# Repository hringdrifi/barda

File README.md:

# Blað

Blað is a compact wireless keyboard design project by [hringdrifi](https://github.com/hringdrifi).

The design uses 42 Kailh Choc hot-swap switch positions and an FDK HY0020 Bluetooth Low Energy module based on the Nordic nRF52832.

## Supported components

The design supports the following keyboard components:

- Kailh Choc V2 switches
- Kailh low-profile sockets
- [Chosfox Cross-Core Low-Profile Stabilizers](https://chosfox.com/products/chosfox-cross-core-satellite-switch-for-low-profile-keyboards)

Confirm the exact part variants and mechanical fit before ordering or manufacturing.

## Connectivity and firmware

Blað has no USB connection and supports Bluetooth Low Energy (BLE) only. It is powered by a CR1632 lithium coin cell. A USB-to-serial adapter is required to flash firmware to the keyboard.

## Project status

The PCB and case design files are published in this repository. Validate the design for your intended switches, battery, firmware, manufacturing process, and assembly before building hardware.

## Available files

- [`pcb/`](pcb/) — KiCad source files for the keyboard PCB and plates
  - [`blad.kicad_pcb`](pcb/blad.kicad_pcb) — main keyboard PCB
  - [`blad.kicad_sch`](pcb/blad.kicad_sch) — schematic
  - [`blad_switch_plate.kicad_pcb`](pcb/blad_switch_plate.kicad_pcb) — switch plate PCB
  - [`blad_bottom_plate.kicad_pcb`](pcb/blad_bottom_plate.kicad_pcb) — bottom plate PCB
  - [`smidr.pretty/`](pcb/smidr.pretty/) — custom footprints referenced by the design
  - [`3dmodels/`](pcb/3dmodels/) — STEP models for selected components
- [`case/`](case/) — STEP models for the case assembly
  - [`blad_switch_plate.step`](case/blad_switch_plate.step) — case switch plate
  - [`blad_bumper.step`](case/blad_bumper.step) — bumper layer
  - [`blad_battery_cap.step`](case/blad_battery_cap.step) — battery cap
- [`pcb/README.md`](pcb/README.md) — Smiðr KiCad-export details
- [`case/README.md`](case/README.md) — case-model notes and file roles

## License

The design data in `pcb/` and `case/` is licensed under the [CERN Open Hardware Licence Version 2 - Permissive (CERN-OHL-P-2.0)](LICENSE).

This license permits use, modification, manufacture, and sale of the design data and products made from it. Modified design data does not need to be published, but applicable notices must be retained and modifications must be documented. The design data and any resulting products are provided without warranty.

## Disclaimer

Verify dimensions, clearances, component compatibility, manufacturability, and safety for your own build before making any parts. Use of these files is at your own risk.

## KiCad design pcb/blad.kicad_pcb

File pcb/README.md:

# Barda KiCad export

Generated by Smiðr.

This KiCad export places center-origin Smiðr switch footprints from the physical layout and emits a matching schematic with keyboard matrix nets.

- Plate PCB: barda_plate.kicad_pcb contains center-origin key-hole footprints for the same physical layout.
- Switch footprint: Smidr:SW_Smidr_Choc_Hotswap
- Diode footprint: Smidr:D_Smidr_SOD123
- Footprint library: smidr.pretty is included in this ZIP and referenced by fp-lib-table.
- Switch outlines: keycap, fab, and courtyard geometry are generated from each key's w/h.
- RGB Matrix: no per-key RGB LEDs placed.
- Backlight: no per-key backlight LEDs placed.
- Direct-pin projects connect each switch between its direct GPIO net and GND.
- Matrix projects connect switches and diodes using ROWn/COLn nets.

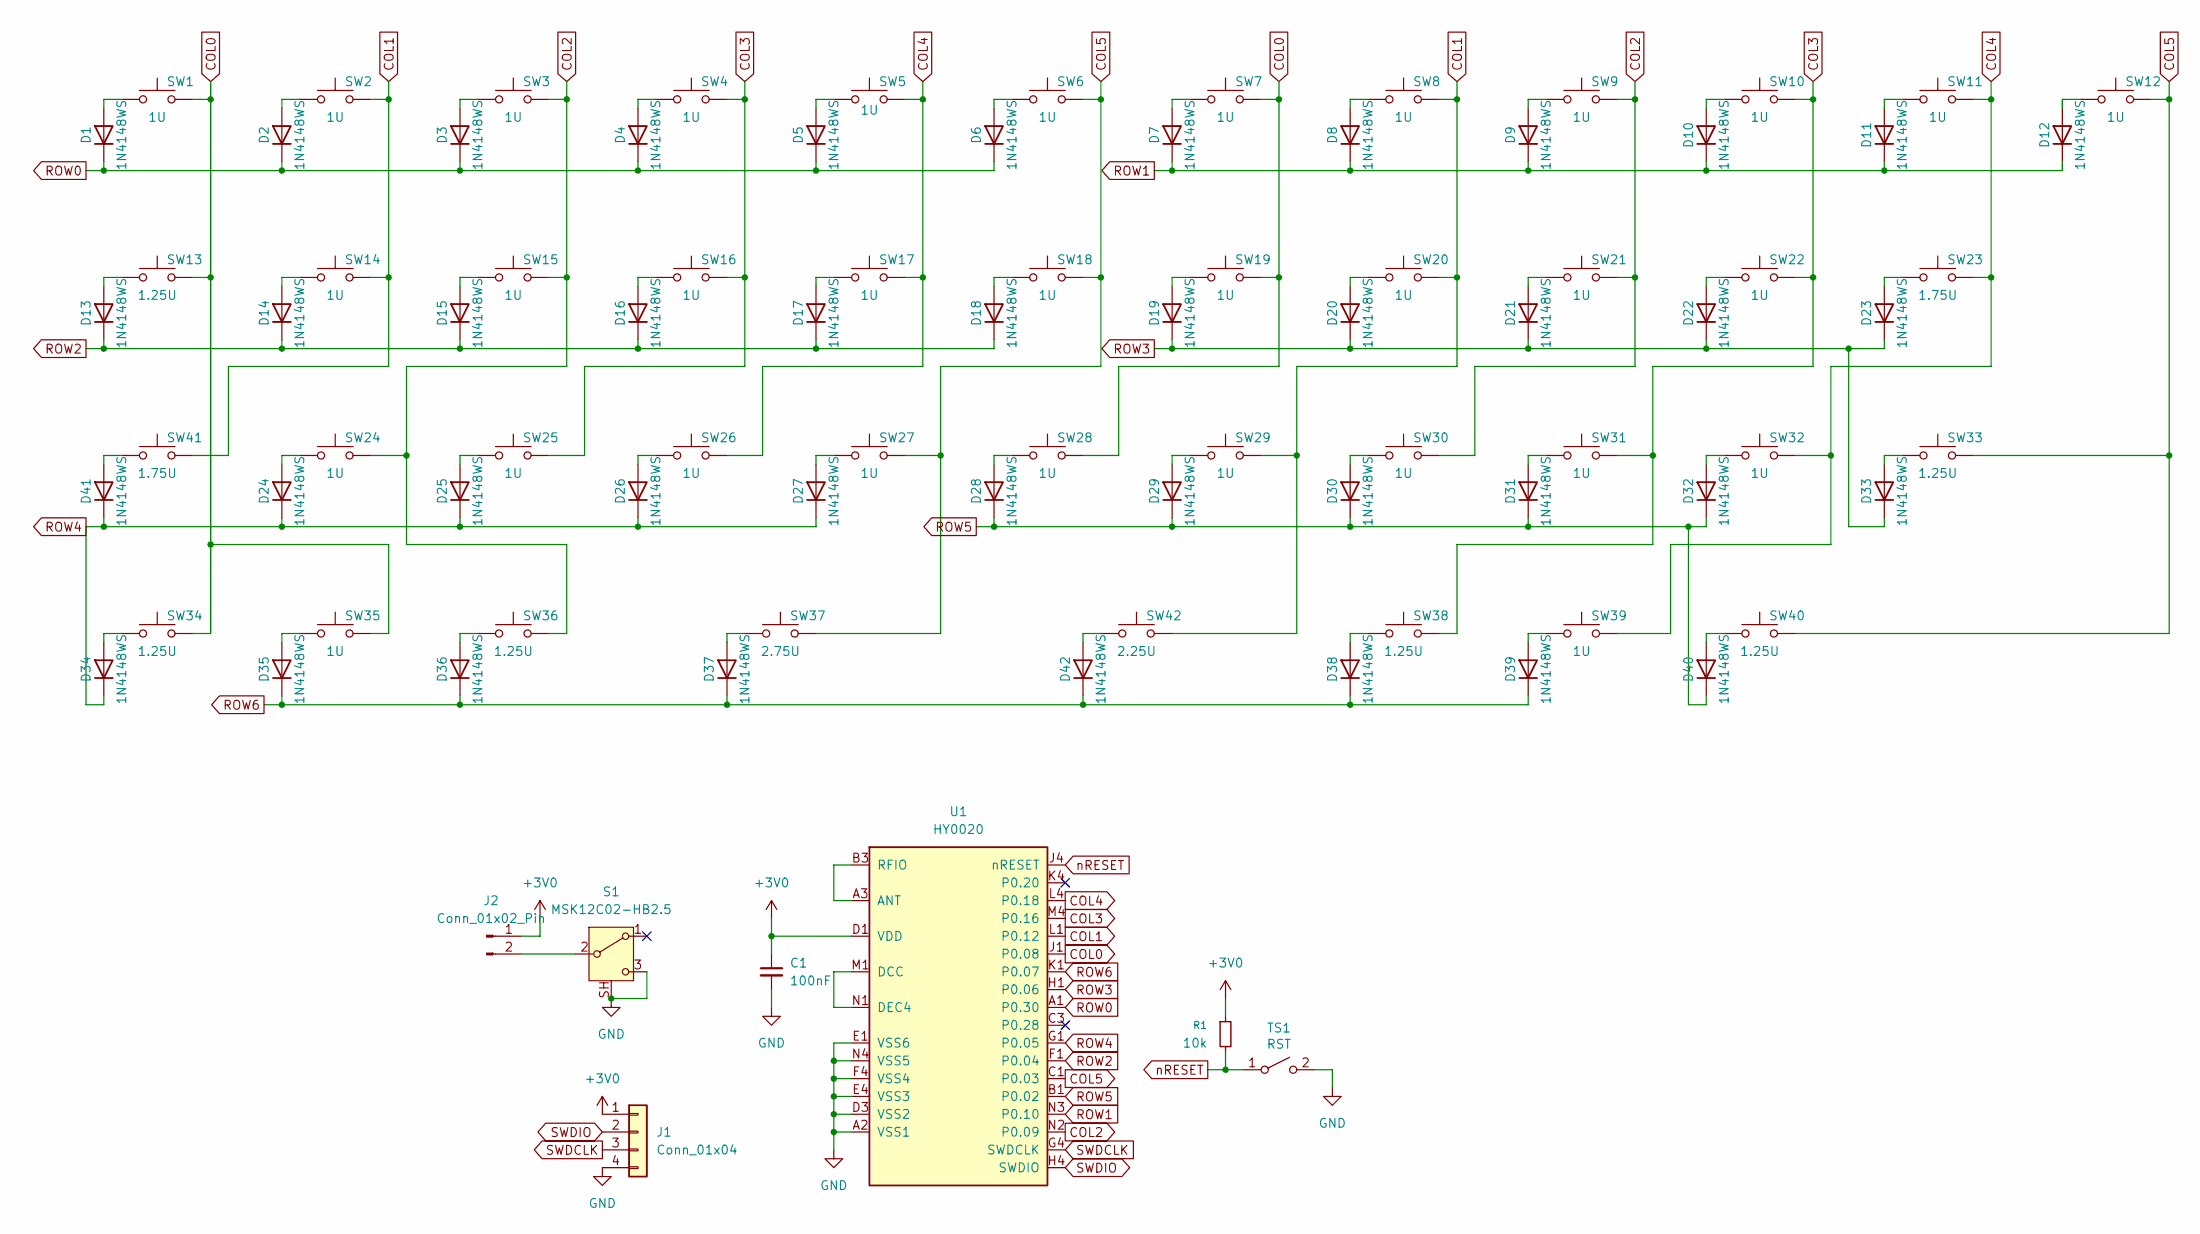
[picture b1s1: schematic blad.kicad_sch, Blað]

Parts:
C1: 100nF; C_0402_1005Metric
D1, D2, D3, D4, D5, D6, D7, D8, D9, D10, D11, D12, D13, D14, D15, D16, D17, D18, D19, D20, D21, D22, D23, D24, D25, D26, D27, D28, D29, D30, D31, D32, D33, D34, D35, D36, D37, D38, D39, D40, D41, D42: 1N4148WS; D_SOD-123
J1: Conn_01x04; PinHeader_1x04_P2.54mm_Vertical
J2: Conn_01x02_Pin; PinHeader_1x02_P2.54mm_Vertical
R1: 10k; R_0402_1005Metric
S1: MSK12C02-HB2.5; SW_SPDT_Shouhan_MSK12C02; JLCPCB Part # C47020937
SW1, SW2, SW3, SW4, SW5, SW6, SW7, SW8, SW9, SW10, SW11, SW12, SW14, SW15, SW16, SW17, SW18, SW19, SW20, SW21, SW22, SW24, SW25, SW26, SW27, SW28, SW29, SW30, SW31, SW32, SW35, SW39: 1U; SW_Smidr_Choc_Hotswap
SW13, SW33, SW34, SW36, SW38, SW40: 1.25U; SW_Smidr_Choc_Hotswap
SW23, SW41: 1.75U; SW_Smidr_Choc_Hotswap
SW37: 2.75U; SW_Smidr_Choc_Hotswap
SW42: 2.25U; SW_Smidr_Choc_Hotswap
TS1: RST; SW_Push_SPST_NO_Alps_SKRK
U1: HY0020; RF_Module_FDK_HY0020

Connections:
+3V0: C1.1, J1.1, J2.1, R1.1, U1.D1 (VDD)
COL0: SW1.2, SW7.2, SW13.2, SW19.2, SW28.2, SW34.2, SW35.2, U1.J1 (P0.08)
COL1: SW2.2, SW8.2, SW14.2, SW20.2, SW29.2, SW41.2, SW42.2, U1.L1 (P0.12)
COL2: SW3.2, SW9.2, SW15.2, SW21.2, SW24.2, SW30.2, SW36.2, U1.N2 (P0.09)
COL3: SW4.2, SW10.2, SW16.2, SW22.2, SW25.2, SW31.2, SW38.2, U1.M4 (P0.16)
COL4: SW5.2, SW11.2, SW17.2, SW23.2, SW26.2, SW32.2, SW39.2, U1.L4 (P0.18)
COL5: SW6.2, SW12.2, SW18.2, SW27.2, SW33.2, SW37.2, SW40.2, U1.C1 (P0.03)
GND: C1.2, J1.4, S1.3 (C), S1.SH, TS1.2 (B), U1.A2 (VSS1), U1.D3 (VSS2), U1.E1 (VSS6), U1.E4 (VSS3), U1.F4 (VSS4), U1.N4 (VSS5)
unnamed: D1.2 (A), SW1.1
unnamed: D2.2 (A), SW2.1
unnamed: D3.2 (A), SW3.1
unnamed: D4.2 (A), SW4.1
unnamed: D5.2 (A), SW5.1
unnamed: D6.2 (A), SW6.1
unnamed: D7.2 (A), SW7.1
unnamed: D8.2 (A), SW8.1
unnamed: D9.2 (A), SW9.1
unnamed: D10.2 (A), SW10.1
unnamed: D11.2 (A), SW11.1
unnamed: D12.2 (A), SW12.1
unnamed: D13.2 (A), SW13.1
unnamed: D14.2 (A), SW14.1
unnamed: D15.2 (A), SW15.1
unnamed: D16.2 (A), SW16.1
unnamed: D17.2 (A), SW17.1
unnamed: D18.2 (A), SW18.1
unnamed: D19.2 (A), SW19.1
unnamed: D20.2 (A), SW20.1
unnamed: D21.2 (A), SW21.1
unnamed: D22.2 (A), SW22.1
unnamed: D23.2 (A), SW23.1
unnamed: D24.2 (A), SW24.1
unnamed: D25.2 (A), SW25.1
unnamed: D26.2 (A), SW26.1
unnamed: D27.2 (A), SW27.1
unnamed: D28.2 (A), SW28.1
unnamed: D29.2 (A), SW29.1
unnamed: D30.2 (A), SW30.1
unnamed: D31.2 (A), SW31.1
unnamed: D32.2 (A), SW32.1
unnamed: D33.2 (A), SW33.1
unnamed: D34.2 (A), SW34.1
unnamed: D35.2 (A), SW35.1
unnamed: D36.2 (A), SW36.1
unnamed: D37.2 (A), SW37.1
unnamed: D38.2 (A), SW38.1
unnamed: D39.2 (A), SW39.1
unnamed: D40.2 (A), SW40.1
unnamed: D41.2 (A), SW41.1
unnamed: D42.2 (A), SW42.1
unnamed: J2.2, S1.2 (B)
unnamed: U1.A3 (ANT), U1.B3 (RFIO)
unnamed: U1.M1 (DCC), U1.N1 (DEC4)
ROW0: D1.1 (K), D2.1 (K), D3.1 (K), D4.1 (K), D5.1 (K), D6.1 (K), U1.A1 (P0.30)
ROW1: D7.1 (K), D8.1 (K), D9.1 (K), D10.1 (K), D11.1 (K), D12.1 (K), U1.N3 (P0.10)
ROW2: D13.1 (K), D14.1 (K), D15.1 (K), D16.1 (K), D17.1 (K), D18.1 (K), U1.F1 (P0.04)
ROW3: D19.1 (K), D20.1 (K), D21.1 (K), D22.1 (K), D23.1 (K), D33.1 (K), U1.H1 (P0.06)
ROW4: D24.1 (K), D25.1 (K), D26.1 (K), D27.1 (K), D34.1 (K), D41.1 (K), U1.G1 (P0.05)
ROW5: D28.1 (K), D29.1 (K), D30.1 (K), D31.1 (K), D32.1 (K), D40.1 (K), U1.B1 (P0.02)
ROW6: D35.1 (K), D36.1 (K), D37.1 (K), D38.1 (K), D39.1 (K), D42.1 (K), U1.K1 (P0.07)
SWDCLK: J1.3, U1.G4 (SWDCLK)
SWDIO: J1.2, U1.H4 (SWDIO)
nRESET: R1.2, TS1.1 (A), U1.J4 (nRESET)

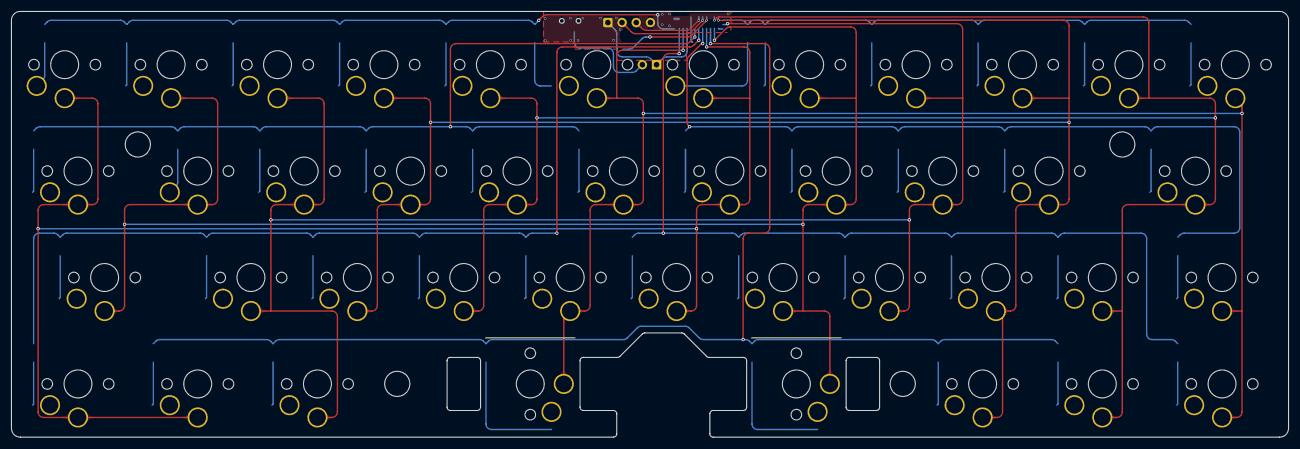
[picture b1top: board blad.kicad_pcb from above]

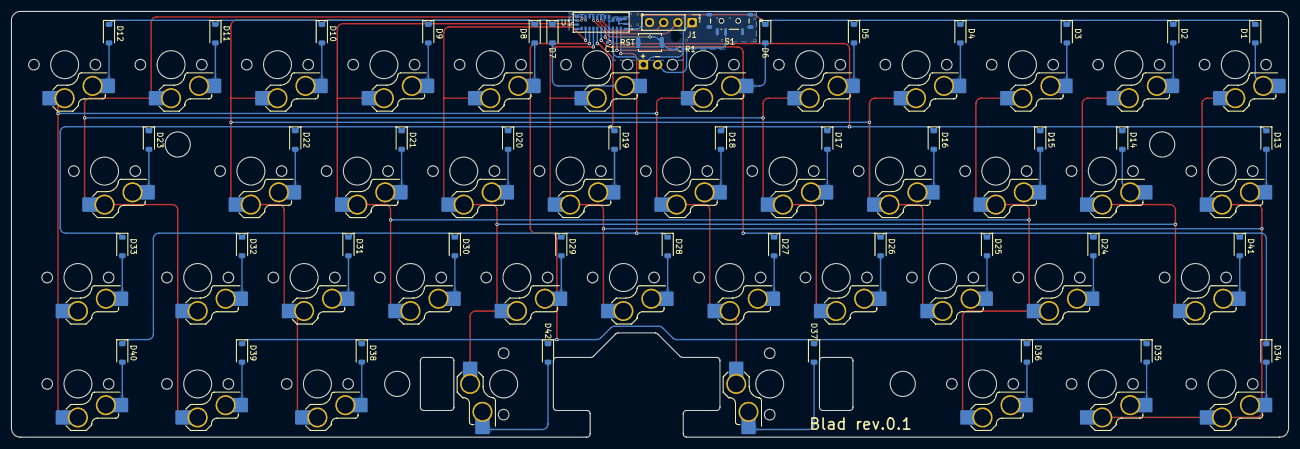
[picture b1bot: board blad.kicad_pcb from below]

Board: 2 copper layers, 228.6 x 76.2 mm, 91 parts (91 on the bottom side), 63 nets.

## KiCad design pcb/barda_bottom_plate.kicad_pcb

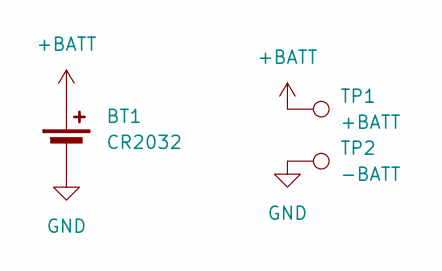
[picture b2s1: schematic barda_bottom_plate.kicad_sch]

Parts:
BT1: CR2032; BAT-SMD_MY-1632-03
TP1: +BATT; TestPoint_Keystone_5019_Miniature
TP2: -BATT; TestPoint_Keystone_5019_Miniature

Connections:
+BATT: BT1.1 (+), TP1.1 (1_1)
GND: BT1.2 (-), TP2.1 (1_1)

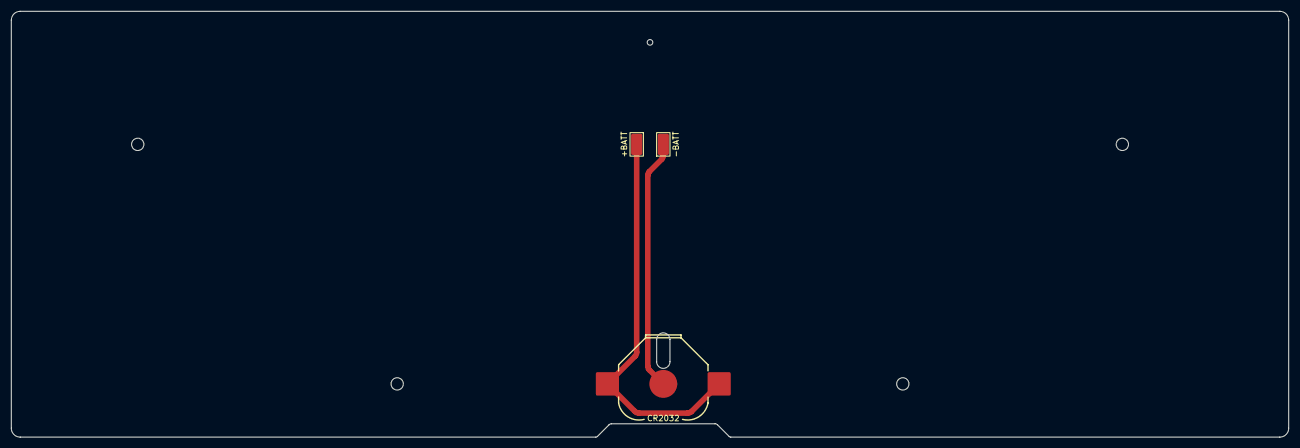
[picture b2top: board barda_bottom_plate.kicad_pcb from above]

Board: 2 copper layers, 228.6 x 76.2 mm, 3 parts (0 on the bottom side), 2 nets.
